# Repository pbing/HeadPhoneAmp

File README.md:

# Headpone amplifier with TPA6120A2

Build on perforated board.
PCB not verified.

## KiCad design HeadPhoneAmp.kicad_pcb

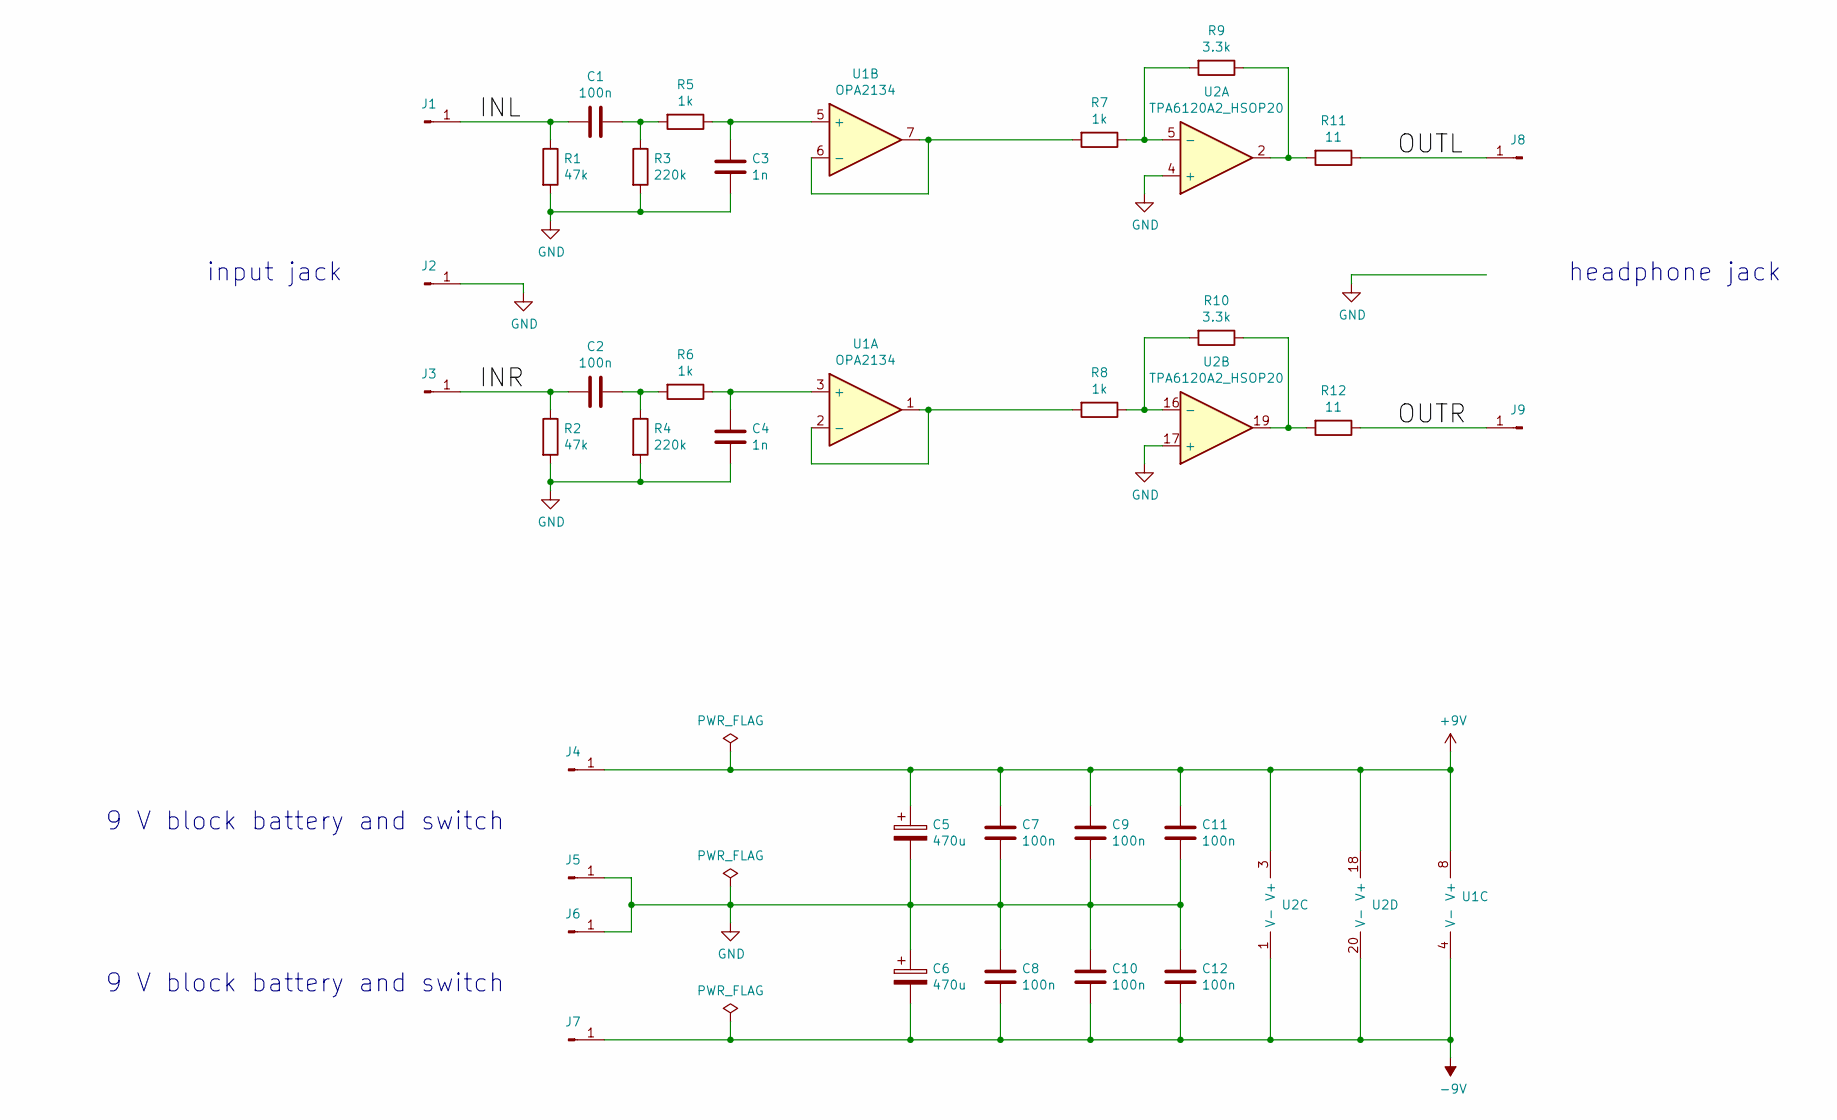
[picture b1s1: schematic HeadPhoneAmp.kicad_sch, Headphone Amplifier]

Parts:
C1, C2, C7, C8, C9, C10, C11, C12: 100n; C_Rect_L7.2mm_W2.5mm_P5.00mm_FKS2_FKP2_MKS2_MKP2
C3, C4: 1n; C_Rect_L4.0mm_W2.5mm_P2.50mm
C5, C6: 470u; CP_Radial_D12.5mm_P5.00mm
J1, J2, J3, J4, J5, J6, J7, J8, J9: Conn_01x01_Male; PinHeader_1x01_P2.54mm_Vertical
R1, R2: 47k; R_Axial_DIN0207_L6.3mm_D2.5mm_P10.16mm_Horizontal
R3, R4: 220k; R_Axial_DIN0207_L6.3mm_D2.5mm_P10.16mm_Horizontal
R5, R6, R7, R8: 1k; R_Axial_DIN0207_L6.3mm_D2.5mm_P10.16mm_Horizontal
R9, R10: 3.3k; R_Axial_DIN0207_L6.3mm_D2.5mm_P10.16mm_Horizontal
R11, R12: 11; R_Axial_DIN0207_L6.3mm_D2.5mm_P10.16mm_Horizontal
U1: OPA2134; DIP-8_W7.62mm
U2: TPA6120A2_HSOP20; HSOP-20-1EP_12.8x7.5mm_P1.27mm

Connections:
+9V: C5.1, C7.2, C9.2, C11.2, J4.1, U1.8 (V+), U2.3 (V+), U2.18 (V+)
-9V: C6.2, C8.1, C10.1, C12.1, J7.1, U1.4 (V-), U2.1 (V-), U2.20 (V-)
/INL: C1.2, J1.1, R1.1
/INR: C2.2, J3.1, R2.1
/OUTL: J8.1, R11.1
/OUTR: J9.1, R12.1
GND: C3.1, C4.1, C5.2, C6.1, C7.1, C8.2, C9.1, C10.2, C11.1, C12.2, J2.1, J5.1, J6.1, R1.2, R2.2, R3.2, R4.2, U2.4 (+), U2.17 (+)
unnamed: C1.1, R3.1, R5.2
unnamed: C2.1, R4.1, R6.2
unnamed: C3.2, R5.1, U1.5 (+)
unnamed: C4.2, R6.1, U1.3 (+)
unnamed: R7.1, R9.2, U2.5 (-)
unnamed: R7.2, U1.6 (-), U1.7
unnamed: R8.2, U1.1, U1.2 (-)
unnamed: R10.1, R12.2, U2.19
unnamed: R8.1, R10.2, U2.16 (-)
unnamed: R9.1, R11.2, U2.2

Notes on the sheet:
input jack
headphone jack
9 V block battery and switch
9 V block battery and switch

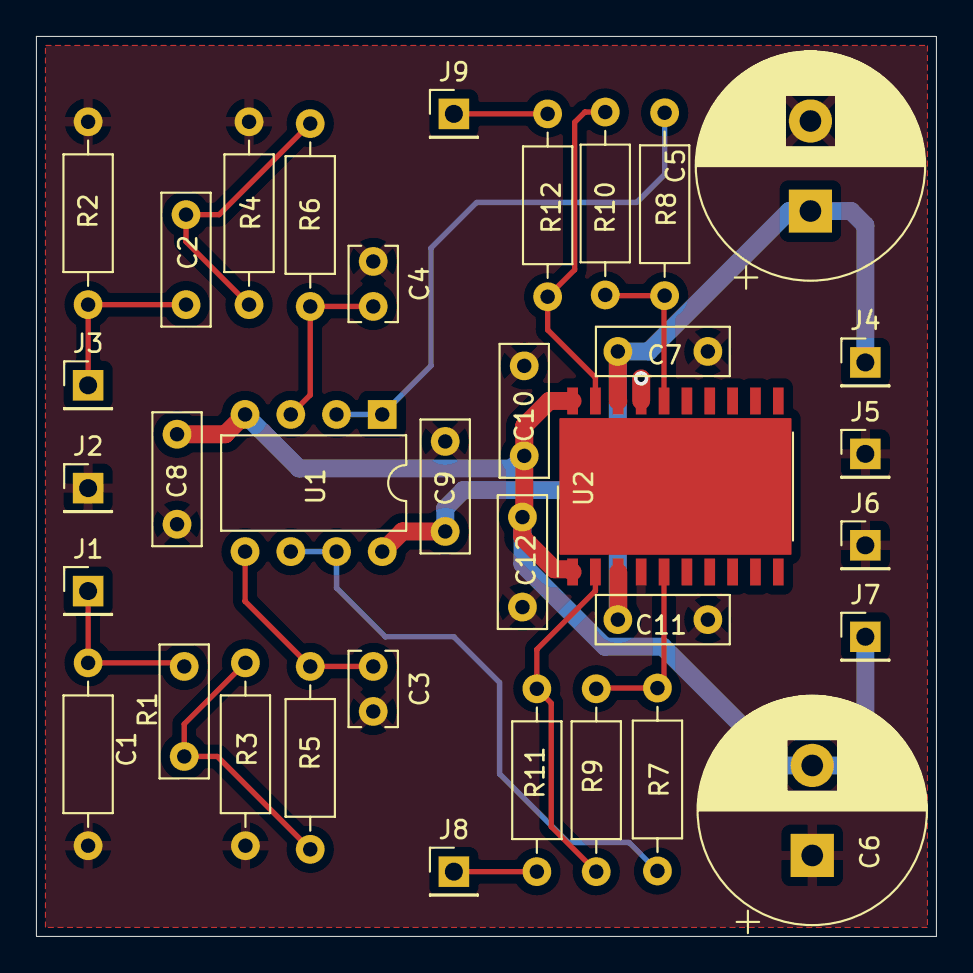
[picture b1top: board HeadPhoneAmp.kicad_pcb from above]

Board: 2 copper layers, 50.0 x 50.0 mm, 35 parts (0 on the bottom side), 17 nets.

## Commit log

2020-05-03 Add PCB
2020-05-03 Update PDF
2020-05-03 Add GND to PCB power
2022-01-30 Bump to KiCad 6
2022-01-30 Added docs again
